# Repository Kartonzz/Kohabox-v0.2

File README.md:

# Kohabox-v0.2
A failed board prototype from a few months ago. Works either off of Waveshare RP2040 Zero with GP2040-CE firmware(https://github.com/OpenStickCommunity/GP2040-CE) or Brook ps3/ps4 square.

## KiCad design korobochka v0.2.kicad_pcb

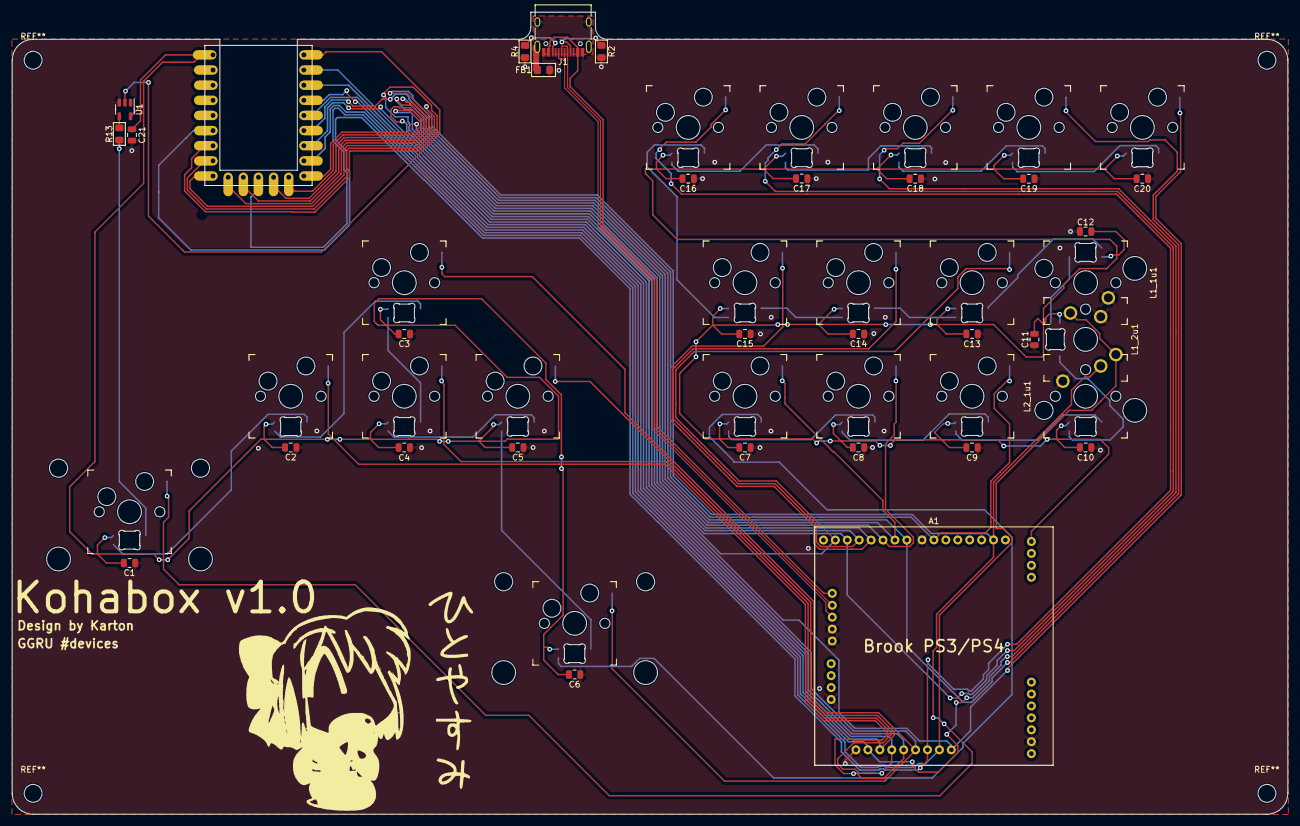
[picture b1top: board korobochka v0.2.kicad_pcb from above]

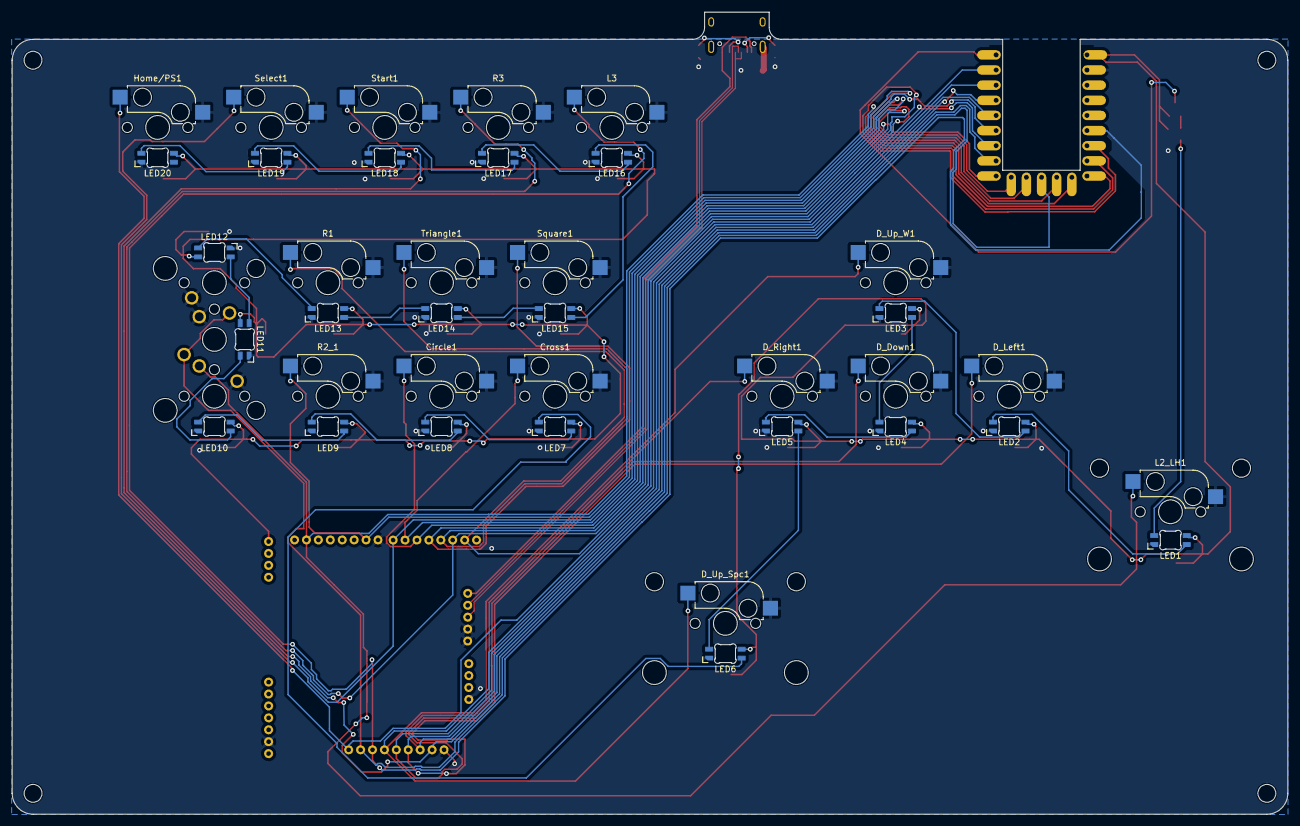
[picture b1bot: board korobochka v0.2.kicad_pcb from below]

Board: 2 copper layers, 214.0 x 134.6 mm, 69 parts (20 on the bottom side), 46 nets.

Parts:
A1: Brook_PS3PS4_PCBA
C1, C2, C3, C4, C5, C6, C7, C8, C9, C10, C11, C12, C13, C14, C15, C16, C17, C18, C19, C20, C21: CP_Generic; C_0805_2012Metric
Circle1: CherryMX; Kailh_socket_MX
Cross1: CherryMX; Kailh_socket_MX
D_Down1: CherryMX; Kailh_socket_MX
D_Left1: CherryMX; Kailh_socket_MX
D_Right1: CherryMX; Kailh_socket_MX
D_Up_Spc1: CherryMX; Kailh_socket_MX
D_Up_W1: CherryMX; Kailh_socket_MX
FB1: FerriteBead_Small; Ferrite_0805_2012Metric_Pad1.15x1.40mm_BigPads
Home/PS1: CherryMX; Kailh_socket_MX
J1: USB_C_Receptacle_USB2.0; USB_C_Receptacle_HRO_TYPE-C-31-M-12
L1_1u1, L1_2u1, L2_1u1: CherryMX; SW_MX
L2_LH1, L3: CherryMX; Kailh_socket_MX
LED1, LED2, LED3, LED4, LED5, LED6, LED7, LED8, LED9, LED10, LED11, LED12, LED13, LED14, LED15, LED16, LED17, LED18, LED19, LED20: SK6812MINI-E; LED_MX_6028R
R1, R2_1, R3: CherryMX; Kailh_socket_MX
R2, R4, R13: R_0805; R_0805_2012Metric_Pad1.15x1.40mm
RZ1: RP2040-Zero; RP2040 Zero changed footprint
Select1: CherryMX; Kailh_socket_MX
Square1: CherryMX; Kailh_socket_MX
Start1: CherryMX; Kailh_socket_MX
Triangle1: CherryMX; Kailh_socket_MX
U1: SN74LV1T34DBV; SOT-23-5

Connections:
Circle: A1.14 (CIRCLE), Circle1.1, RZ1.13 (GP12)
Cross: A1.15 (CROSS), Cross1.1, RZ1.14 (GP13)
DIN: LED1.3 (DIN), R13.1
DOUT: RZ1.1 (GP0), U1.2 (A)
D_Down: A1.5 (D_Down), D_Down1.1, RZ1.3 (GP2)
D_Left: A1.4 (D_Left), D_Left1.1, RZ1.5 (GP4)
D_Right: A1.3 (D_Right), D_Right1.1, RZ1.4 (GP3)
D_Up: A1.6 (D_Up), D_Up_Spc1.1, D_Up_W1.1, RZ1.2 (GP1)
GND: A1.1 (GND), C1.2, C2.2, C3.2, C4.2, C5.2, C6.2, C7.2, C8.2, C9.2, C10.2, C11.2, C12.2, C13.2, C14.2, C15.2, C16.2, C17.2, C18.2, C19.2, C20.2, C21.2, Circle1.2, Cross1.2, D_Down1.2, D_Left1.2, D_Right1.2, D_Up_Spc1.2, D_Up_W1.2, FB1.1, Home/PS1.2, J1.A1 (GND), J1.A12 (GND), J1.B1 (GND), J1.B12 (GND), L1_1u1.2, L1_2u1.2, L2_1u1.2, L2_LH1.2, L3.2, LED1.4 (VSS), LED2.4 (VSS), LED3.4 (VSS), LED4.4 (VSS), LED5.4 (VSS), LED6.4 (VSS), LED7.4 (VSS), LED8.4 (VSS), LED9.4 (VSS), LED10.4 (VSS), LED11.4 (VSS), LED12.4 (VSS), LED13.4 (VSS), LED14.4 (VSS), LED15.4 (VSS), LED16.4 (VSS), LED17.4 (VSS), LED18.4 (VSS), LED19.4 (VSS), LED20.4 (VSS), R1.2, R2.1, R2_1.2, R3.2, R4.1, RZ1.23 (GND), Select1.2, Square1.2, Start1.2, Triangle1.2, U1.3 (GND)
Home: A1.9 (PS_Key), Home/PS1.1, RZ1.7 (GP6)
L1: A1.8 (L1), L1_1u1.1, L1_2u1.1, RZ1.12 (GP11)
L2: A1.22 (L2), L2_1u1.1, L2_LH1.1, RZ1.16 (GP15)
L3: A1.7 (L3), L3.1, RZ1.18 (GP27)
unnamed: J1.A5 (CC1), R2.2
unnamed: J1.B5 (CC2), R4.2
unnamed: FB1.2, J1.S1 (SHIELD)
unnamed: LED1.2 (DOUT), LED2.3 (DIN)
unnamed: LED2.2 (DOUT), LED3.3 (DIN)
unnamed: LED3.2 (DOUT), LED4.3 (DIN)
unnamed: LED4.2 (DOUT), LED5.3 (DIN)
unnamed: LED5.2 (DOUT), LED6.3 (DIN)
unnamed: LED6.2 (DOUT), LED7.3 (DIN)
unnamed: LED7.2 (DOUT), LED8.3 (DIN)
unnamed: LED8.2 (DOUT), LED9.3 (DIN)
unnamed: LED9.2 (DOUT), LED10.3 (DIN)
unnamed: LED10.2 (DOUT), LED11.3 (DIN)
unnamed: LED11.2 (DOUT), LED12.3 (DIN)
unnamed: LED12.2 (DOUT), LED13.3 (DIN)
unnamed: LED13.2 (DOUT), LED14.3 (DIN)
unnamed: LED14.2 (DOUT), LED15.3 (DIN)
unnamed: LED15.2 (DOUT), LED16.3 (DIN)
unnamed: LED16.2 (DOUT), LED17.3 (DIN)
unnamed: LED17.2 (DOUT), LED18.3 (DIN)
unnamed: LED18.2 (DOUT), LED19.3 (DIN)
unnamed: LED19.2 (DOUT), LED20.3 (DIN)
unnamed: R13.2, U1.4 (Y)
R1: A1.10 (R1), R1.1, RZ1.11 (GP10)
R2: A1.17 (R2), R2_1.1, RZ1.15 (GP14)
R3: A1.11 (R3), R3.1, RZ1.17 (GP26)
Select: A1.16 (SHARE), RZ1.6 (GP5), Select1.1
Square: A1.13 (SQUARE), RZ1.9 (GP8), Square1.1
Start: A1.2 (Options), RZ1.8 (GP7), Start1.1
Triangle: A1.12 (TRIANGLE), RZ1.10 (GP9), Triangle1.1
USB_D+: A1.28 (USB_D+), J1.A6 (D+), J1.B6 (D+)
USB_D-: A1.29 (USB_D-), J1.A7 (D-), J1.B7 (D-)
VBUS: A1.35 (VDD_5V), C1.1, C2.1, C3.1, C4.1, C5.1, C6.1, C7.1, C8.1, C9.1, C10.1, C11.1, C12.1, C13.1, C14.1, C15.1, C16.1, C17.1, C18.1, C19.1, C20.1, C21.1, J1.A4 (VBUS), J1.A9 (VBUS), J1.B4 (VBUS), J1.B9 (VBUS), LED1.1 (VDD), LED2.1 (VDD), LED3.1 (VDD), LED4.1 (VDD), LED5.1 (VDD), LED6.1 (VDD), LED7.1 (VDD), LED8.1 (VDD), LED9.1 (VDD), LED10.1 (VDD), LED11.1 (VDD), LED12.1 (VDD), LED13.1 (VDD), LED14.1 (VDD), LED15.1 (VDD), LED16.1 (VDD), LED17.1 (VDD), LED18.1 (VDD), LED19.1 (VDD), LED20.1 (VDD), RZ1.22 (5V), U1.5 (VCC)

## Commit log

2023-10-27 Added main files
